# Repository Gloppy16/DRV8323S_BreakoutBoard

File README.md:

# DRV8323S_BreakoutBoard

Simple DRV8323S Breakout board. 
Untested and designed by someone with little experience. Use at your own risk.

30v 60a mosfets. I dont recommend pushing the board that hard however.

I'll probably post updates with safe limits for the board as I test it.

The DRV8323S supports using the fets as current shunts. Cut the three jumpers and short the current shunts if you want to try that.

[Relavant forum post here https://community.simplefoc.com/t/drv8323-breakout-board/5608](https://community.simplefoc.com/t/drv8323s-breakout-board-attempt-2-requests-for-comment/5649/2)

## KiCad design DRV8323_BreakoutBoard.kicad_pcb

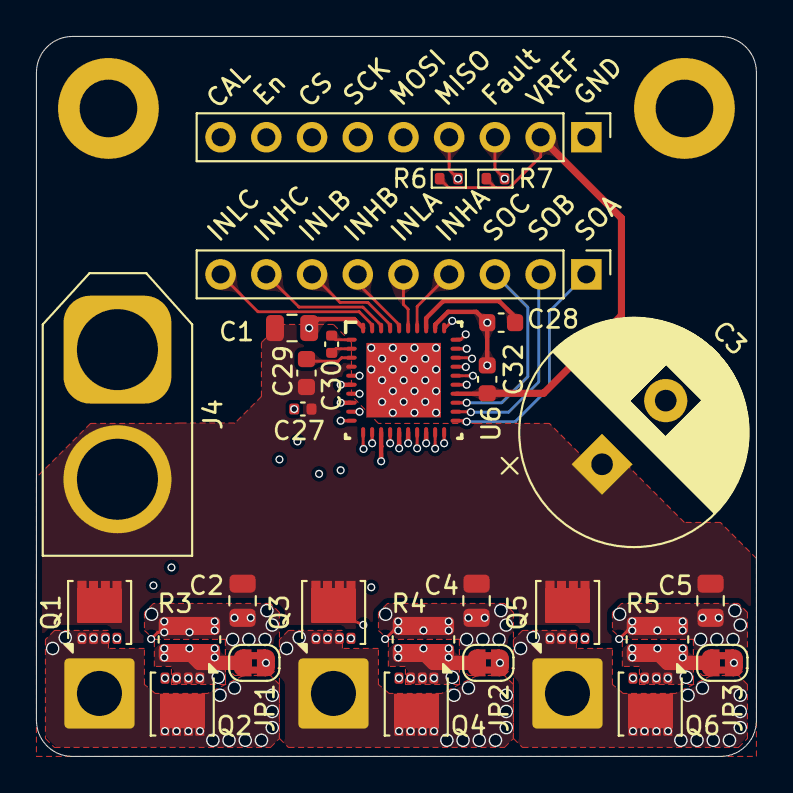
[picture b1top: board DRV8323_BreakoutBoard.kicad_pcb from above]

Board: 6 copper layers, 40.0 x 40.0 mm, 37 parts (0 on the bottom side), 42 nets.

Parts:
C1, C2, C4, C5: C_0805_10uF; C_0805_2012Metric
C3: Cap_D12.5mm_1000uF; CP_Radial_D12.5mm_P5.00mm
C27: C_0402_0.1uf; C_0402_1005Metric
C28, C29, C32: C_0603_1uF; C_0603_1608Metric
C30: C_47nF_0402; C_0402_1005Metric
H1, H2: MountingHole; MountingHole_3.2mm_M3_DIN965_Pad
J2, J6: Conn_01x09_Pin; PinHeader_1x09_P2.54mm_Vertical
J4: Conn_01x02_Pin; AMASS_XT60-M_1x02_P7.20mm_Vertical
JP1, JP2, JP3: Jumper_Bridge; SolderJumper-2_P1.3mm_Bridged2Bar_RoundedPad1.0x1.5mm
MA1: Conn_01x01_Pin; SolderWire-2sqmm_1x01_D2mm_OD3.9mm
MB2: Conn_01x01_Pin; SolderWire-2sqmm_1x01_D2mm_OD3.9mm
MC3: Conn_01x01_Pin; SolderWire-2sqmm_1x01_D2mm_OD3.9mm
NT1, NT2, NT3, NT4: NetTie; NetTie-2_0.16.mm_Diam
Q1, Q2, Q3, Q4, Q5, Q6: 30v_60a_Mosfet; VSON-8_3.3x3.3mm_P0.65mm_NexFET
R3, R4, R5: R_0612_1mOhm; R_0612_1632Metric
R6, R7: R_0402_10k; R_0402_1005Metric
U6: DRV8323S; RTA0040B_NV

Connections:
/SPA_JP: JP1.1 (A), Q2.1 (S), Q2.2 (S), Q2.3 (S), R3.1
/SPB_JP: JP2.1 (A), Q4.1 (S), Q4.2 (S), Q4.3 (S), R4.1
/SPC_JP: JP3.1 (A), Q6.1 (S), Q6.2 (S), Q6.3 (S), R5.1
CAL: J2.9, U6.31 (CAL)
CS: J2.7, U6.29 (GAIN_SCS_N)
Enable: J2.8, U6.30 (ENABLE)
GHA: Q1.4 (G), U6.6 (GHA)
GHB: Q3.4 (G), U6.15 (GHB)
GHC: Q5.4 (G), U6.16 (GHC)
GLA: Q2.4 (G), U6.8 (GLA)
GLB: Q4.4 (G), U6.13 (GLB)
GLC: Q6.4 (G), U6.18 (GLC)
GND: C1.1, C2.1, C3.2, C4.1, C5.1, C27.1, C28.1, C32.2, J2.1, J4.1, NT2.2, NT3.2, NT4.2, R3.2, R4.2, R5.2, U6.32 (AGND), U6.40 (PGND), U6.41 (PAD)
INHA: J6.4, U6.34 (INHA)
INHB: J6.6, U6.36 (INHB)
INHC: J6.8, U6.38 (INHC)
INLA: J6.5, U6.35 (INLA)
INLB: J6.7, U6.37 (INLB)
INLC: J6.9, U6.39 (INLC)
MA: MA1.1, Q1.1 (S), Q1.2 (S), Q1.3 (S), Q2.5 (D), U6.7 (SHA)
MB: MB2.1, Q3.1 (S), Q3.2 (S), Q3.3 (S), Q4.5 (D), U6.14 (SHB)
MC: MC3.1, Q5.1 (S), Q5.2 (S), Q5.3 (S), Q6.5 (D), U6.17 (SHC)
MISO: J2.4, R6.1, U6.26 (MODE_SDO)
MOSI: J2.5, U6.27 (IDRIVE_SDI)
unnamed: C30.1, U6.2 (CPH)
unnamed: C30.2, U6.1 (CPL)
unnamed: C28.2, U6.33 (DVDD)
unnamed: C29.2, U6.3 (VCP)
SCK: J2.6, U6.28 (VDS_SCLK)
SNA: NT2.1, U6.10 (SNA)
SNB: NT3.1, U6.11 (SNB)
SNC: NT4.1, U6.20 (SNC)
SOA: J6.3, U6.23 (SOA)
SOB: J6.2, U6.22 (SOB)
SOC: J6.1, U6.21 (SOC)
SPA: JP1.2 (B), U6.9 (SPA)
SPB: JP2.2 (B), U6.12 (SPB)
SPC: JP3.2 (B), U6.19 (SPC)
VDRAIN: NT1.2, U6.5 (VDRAIN)
VIN: C1.2, C2.2, C3.1, C4.2, C5.2, C27.2, C29.1, J4.2, NT1.1, Q1.5 (D), Q3.5 (D), Q5.5 (D), U6.4 (VM)
VREF: C32.1, J2.2, R6.2, R7.2, U6.24 (VREF)
nFault: J2.3, R7.1, U6.25 (FAULT_N)

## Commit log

2024-10-07 Added Files
2024-10-12 Delete Manufacturing Files directory as its out of date
    The board isn't ready anyway
